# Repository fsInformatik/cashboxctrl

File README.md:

cashboxctrl
===========

Cash Box Controll

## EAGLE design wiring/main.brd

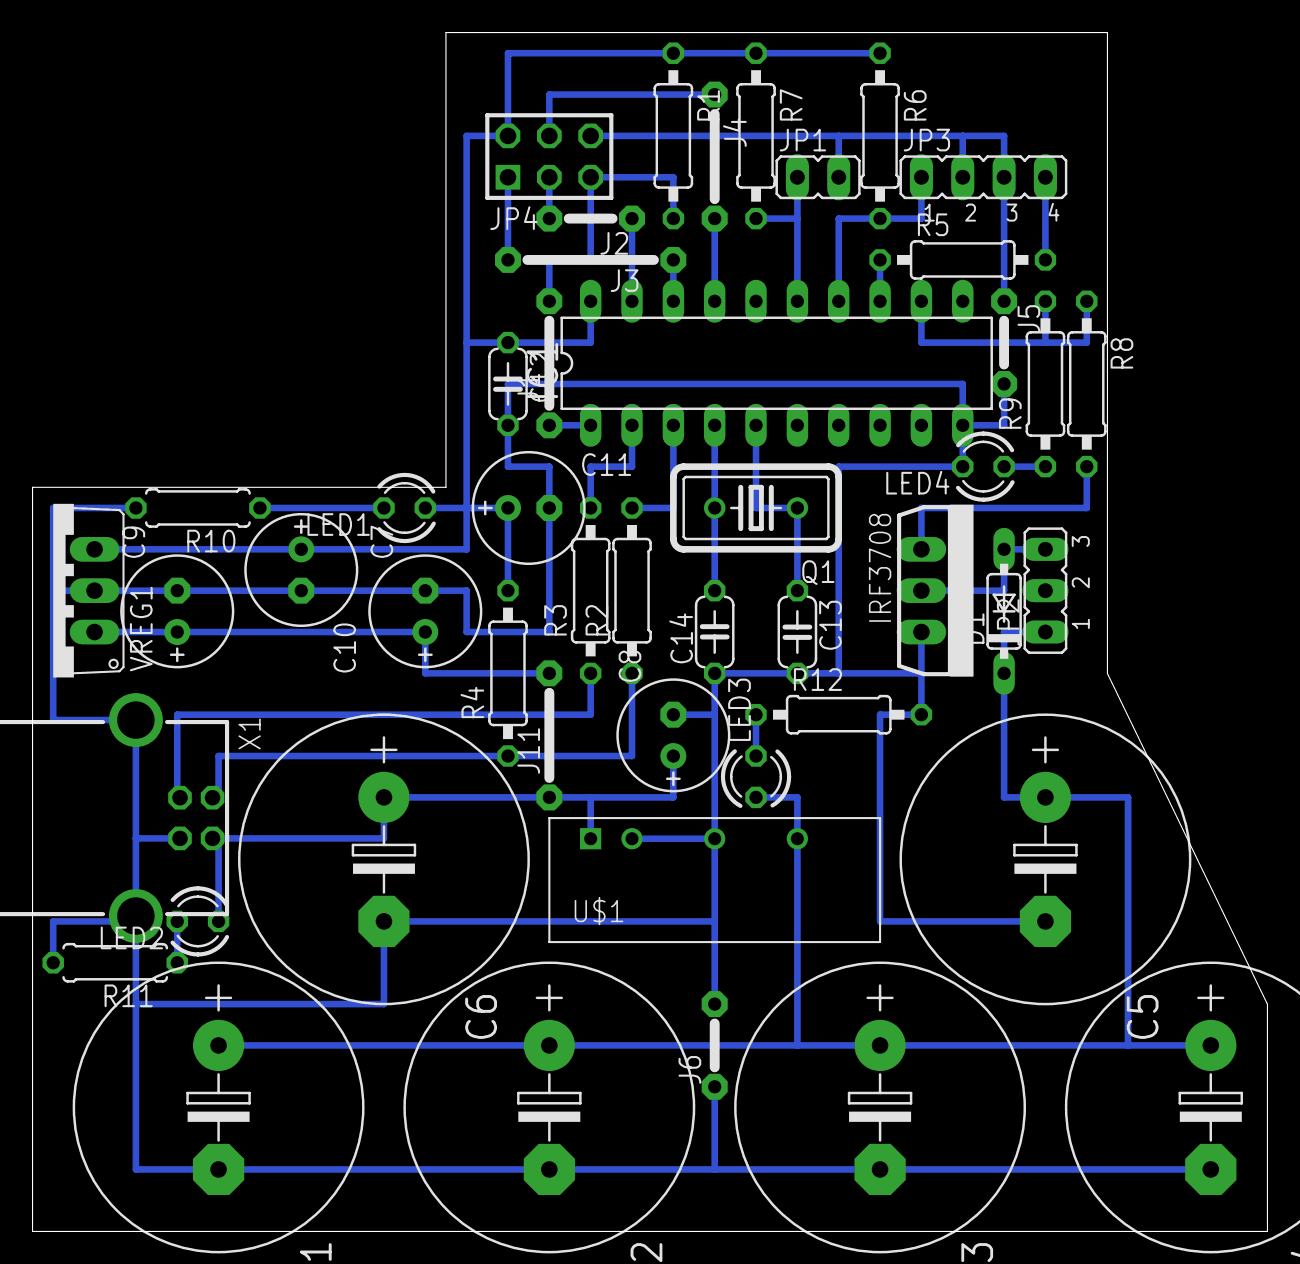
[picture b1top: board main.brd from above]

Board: 2 copper layers, 75.9 x 73.7 mm, 48 parts (0 on the bottom side), 25 nets.

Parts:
C1, C2, C3, C4, C5, C6: 6.800µ; E7,5-18
C7, C8, C10: 220µ; E2,5-7
C9, C11: 68µ; E2,5-7
C12: 330p; C050-024X044
C13, C14: 22p; C050-024X044
D1: 1N4148DO35-7; DO35-7
IC1: attiny 2313A; DIL20
IRF3708: IRF3704L-V; TO262-V
J1, J4, J11: J7MM; 07
J2, J5, J6: J5MM; 05
J3: J10MM; 10
JP1: Taster; JP1
JP2: Spule; JP2
JP3: Lichtschranke; JP4
JP4: AVR-ISP-6VERT; AVR-ISP-6
LED1, LED2, LED4: LED3MM
LED3: LED 3MM 2MA GN; LED3MM
Q1: 12MHz; HC18U-V
R1, R6, R7: 10k; 0207/10
R2, R3, R5: 68; 0207/10
R4: 1,5k; 0207/10
R8: 100; 0207/10
R9: 649; 0207/10
R10: 649; 0207/7
R11: 1,5k; 0207/7
R12: 6,49k; 0207/10
U$1: SIM2-0515S; SIL7
VREG1: LF33CVV; TO220V
X1: USB-B

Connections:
+3V3: C10.+, C11.+, C12.1, IC1.20, JP4.2, LED1.A, R1.1, R4.2, R6.1, R7.1, VREG1.3
+5V: C6.+, C7.+, C8.+, C9.+, J11.1, J11.2, LED2.A, U$1.PIN1, VREG1.1, X1.1
+15V: C1.+, C2.+, C3.+, C4.+, C5.+, D1.C, JP2.1, LED3.A, U$1.PIN6
D+: R3.1, X1.3
D-: R2.1, R4.1, X1.2
GND: C1.-, C2.-, C3.-, C4.-, C5.-, C6.-, C7.-, C8.-, C9.-, C10.-, C11.-, C12.2, C13.2, C14.1, IC1.10, IRF3708.3, J5.1, J5.2, J6.1, J6.2, JP1.2, JP3.2, JP3.3, JP4.6, LED4.K, R10.2, R11.2, R12.2, U$1.PIN2, U$1.PIN4, VREG1.2, X1.4, X1.S1, X1.S2
MISO: IC1.18, J3.1, J3.2, JP4.1
MOSI: IC1.17, J4.1, J4.2, JP4.4
unnamed: LED3.K, R12.1
unnamed: IRF3708.1, R8.2
unnamed: D1.A, IRF3708.2, JP2.3
unnamed: LED2.K, R11.1
unnamed: LED1.K, R10.1
unnamed: LED4.A, R9.1
unnamed: JP3.4, R5.2
unnamed: C13.1, IC1.5, Q1.1
unnamed: C14.2, IC1.4, Q1.2
unnamed: IC1.15, JP1.1, R7.2
unnamed: IC1.13, R5.1
unnamed: IC1.14, JP3.1, R6.2
unnamed: IC1.2, R3.2
unnamed: IC1.3, R2.2
PB0: IC1.12, R8.1, R9.2
RST: IC1.1, J1.1, J1.2, JP4.5, R1.2
SCK: IC1.19, J2.1, J2.2, JP4.3

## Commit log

2013-03-23 add datasheets ATtiny2313...
2013-03-23 add eagle wiring
2013-03-23 add wiring/board.png
2013-03-23 ändern auf mosfet
2013-03-24 add in development sources for host program and avr firmware
2013-03-24 zwischenspeichern schaltplan schöner zeichnen
2013-03-24 schaltplan überarbeitet
2013-03-24 add datasheet sim2sil7
2013-03-25 add datasheet tcst2103
2013-03-25 add datasheet irf3708
2013-03-25 kleine Aenderungen
2013-03-26 wiring power led eingezeichnet
2013-03-26 wiring schaltazeige led eingezeichnet
2013-03-27 wiring schaltazeige led Widerstand geändert
